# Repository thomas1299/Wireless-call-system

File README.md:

# Wireless-call-system
Die drahtlos angesteuerte Rufanlage dient zum Absetzen eines Notrufs, welche speziell für Menschen mit Einschränkungen der oberen Gliedmaßen entwickelt wurde. Anstatt wie bei herkömmlichen Rufanlagen, wo eine Taste gedrückt werden muss, um den Alarm auszulösen, erfolgt bei dieser Rufanlage die Alarmauslösung über Messung der Temperatur. Die Rufanlage ist in der Lage durch Messung der Temperatur zu erkennen, ob der Sensor zwischen die Lippen genommen wurde oder nicht, um so einen Alarm auszulösen. Der Alarm wird am Basisgerät, an welchem der Temperatursensor angeschlossen ist und am mobilen Empfangsgerät ausgelöst.

Die Alarmauslösung auf beiden Geräten erfolgt innerhalb von 500 ms ab dem Berühren des Sensors durch die Lippen und die Reichweite der Funkverbindung beträgt mindestens 100 m im Freien. Beide Geräte können mit einem Li-Ionen-Akku der Größe 18650 mit 3,7 V versorgt werden.

Die Rufanlage wurde so entwickelt dass diese möglichst Kostengünstig und einfach nachzubauen ist.

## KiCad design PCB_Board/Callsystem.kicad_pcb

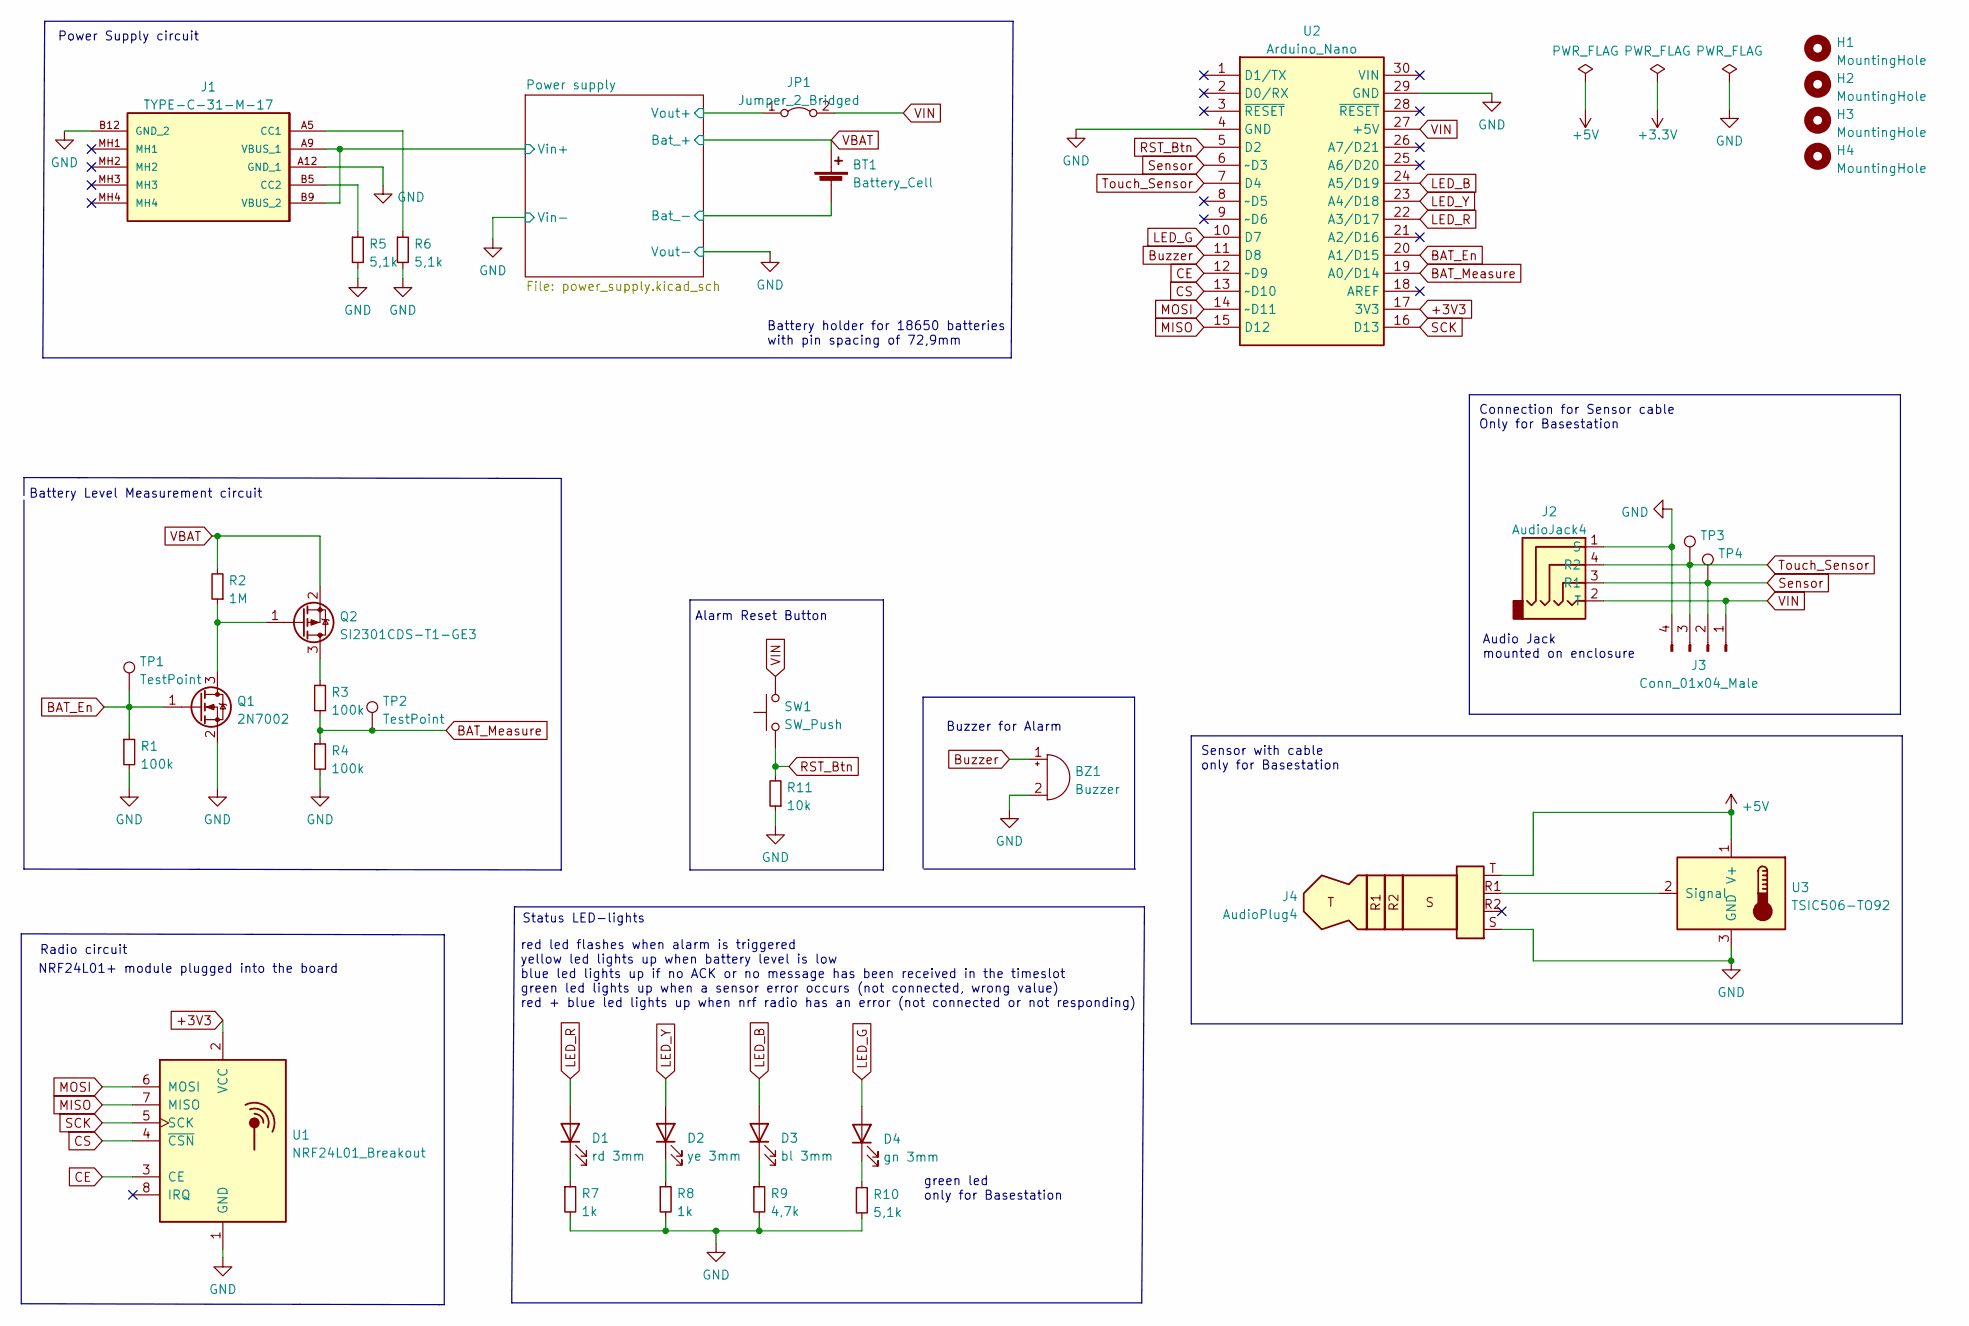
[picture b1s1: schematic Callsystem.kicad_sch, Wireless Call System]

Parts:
BT1: Battery_Cell; BatteryHolder_MPD_BH-18650-PC2
BZ1: Buzzer; Buzzer_12x9.5RM7.6; LCSC C96222
D1: rd 3mm; PinHeader_1x02_P2.54mm_Vertical; LCSC C234182
D2: ye 3mm; PinHeader_1x02_P2.54mm_Vertical; LCSC C234182
D3: bl 3mm; PinHeader_1x02_P2.54mm_Vertical; LCSC C234182
D4: gn 3mm; PinHeader_1x02_P2.54mm_Vertical; LCSC C234182
H1, H2, H3, H4: MountingHole; MountingHole_3.2mm_M3
J1: TYPE-C-31-M-17; TYPEC31M17_new; MANUFACTURER_PART_NUMBER TYPE-C-31-M-17; LCSC C283540
J2: AudioJack4; PinHeader_1x04_P2.54mm_Vertical
J3: Conn_01x04_Male; PinHeader_1x04_P2.54mm_Vertical; LCSC C2905435
J4: AudioPlug4
JP1: Jumper_2_Bridged; PinHeader_1x02_P2.54mm_Vertical; LCSC C234182
Q1: 2N7002; SOT-23; LCSC C8545
Q2: SI2301CDS-T1-GE3; SOT-23; LCSC C10487
R1, R3, R4: 100k; R_0805_2012Metric; LCSC C149504
R2: 1M; R_0805_2012Metric; LCSC C17514
R5, R6, R10: 5,1k; R_0805_2012Metric; LCSC C27834
R7, R8: 1k; R_0805_2012Metric; LCSC C17513
R9: 4,7k; R_0805_2012Metric; LCSC C17673
R11: 10k; R_0805_2012Metric; LCSC C17414
SW1: SW_Push; PinHeader_1x02_P2.54mm_Vertical; LCSC C234182
TP1, TP2, TP3, TP4: TestPoint; TestPoint_Pad_D1.0mm
U1: NRF24L01_Breakout; nRF24L01_LNA_Module; LCSC C239344
U2: Arduino_Nano
U3: TSIC506-TO92; TO-92_Inline

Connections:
+3V3: U1.2 (VCC), U2.17 (3V3)
/Power supply/Bat_-: BT1.2 (-); also elsewhere on the board
/Power supply/Vin+: J1.A9 (VBUS_1), J1.B9 (VBUS_2); also elsewhere on the board
/Power supply/Vout+: JP1.1 (A); also elsewhere on the board
BAT_En: Q1.1 (G), R1.1, TP1.1, U2.20 (A1/D15)
BAT_Measure: R3.2, R4.1, TP2.1, U2.19 (A0/D14)
Buzzer: BZ1.1 (-), U2.11 (D8)
CE: U1.3 (CE), U2.12 (~D9)
CS: U1.4 (~CSN), U2.13 (~D10)
GND: BZ1.2 (+), J1.A12 (GND_1), J1.B12 (GND_2), J2.1 (S), J3.4, J4.S, Q1.2 (S), R1.2, R4.2, R5.2, R6.2, R7.2, R8.2, R9.2, R10.2, R11.1, U1.1 (GND), U2.4 (GND), U2.29 (GND), U3.3 (GND); also elsewhere on the board
LED_B: D3.2 (A), U2.24 (A5/D19)
LED_G: D4.2 (A), U2.10 (D7)
LED_R: D1.2 (A), U2.22 (A3/D17)
LED_Y: D2.2 (A), U2.23 (A4/D18)
MISO: U1.7 (MISO), U2.15 (D12)
MOSI: U1.6 (MOSI), U2.14 (~D11)
unnamed: D1.1 (K), R7.1
unnamed: D2.1 (K), R8.1
unnamed: D3.1 (K), R9.1
unnamed: D4.1 (K), R10.1
unnamed: J1.A5 (CC1), R6.1
unnamed: J1.B5 (CC2), R5.1
unnamed: J4.R1, U3.2 (Signal)
unnamed: J4.T, U3.1 (V+)
unnamed: Q1.3 (D), Q2.1 (G), R2.1
unnamed: Q2.3 (D), R3.1
RST_Btn: R11.2, SW1.1, U2.5 (D2)
SCK: U1.5 (SCK), U2.16 (D13)
Sensor: J2.3 (R1), J3.2, TP4.1, U2.6 (~D3)
Touch_Sensor: J2.4 (R2), J3.3, TP3.1, U2.7 (D4)
VBAT: BT1.1 (+), Q2.2 (S), R2.2; also elsewhere on the board
VIN: J2.2 (T), J3.1, JP1.2 (B), SW1.2, U2.27 (+5V)

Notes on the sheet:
Radio circuit
Status LED-lights
Buzzer for Alarm
red led flashes when alarm is triggered yellow led lights up when battery level is low blue led lights up if no ACK or no message has been received in the timeslot green led lights up when a sensor error occurs (not connected, wrong value) red + blue led lights up when nrf radio has an error (not c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
NRF24L01+ module plugged into the board
Battery Level Measurement circuit
Sensor with cable only for Basestation
Battery holder for 18650 batteries with pin spacing of 72,9mm
Audio Jack mounted on enclosure
Power Supply circuit
green led only for Basestation
Connection for Sensor cable Only for Basestation
Alarm Reset Button

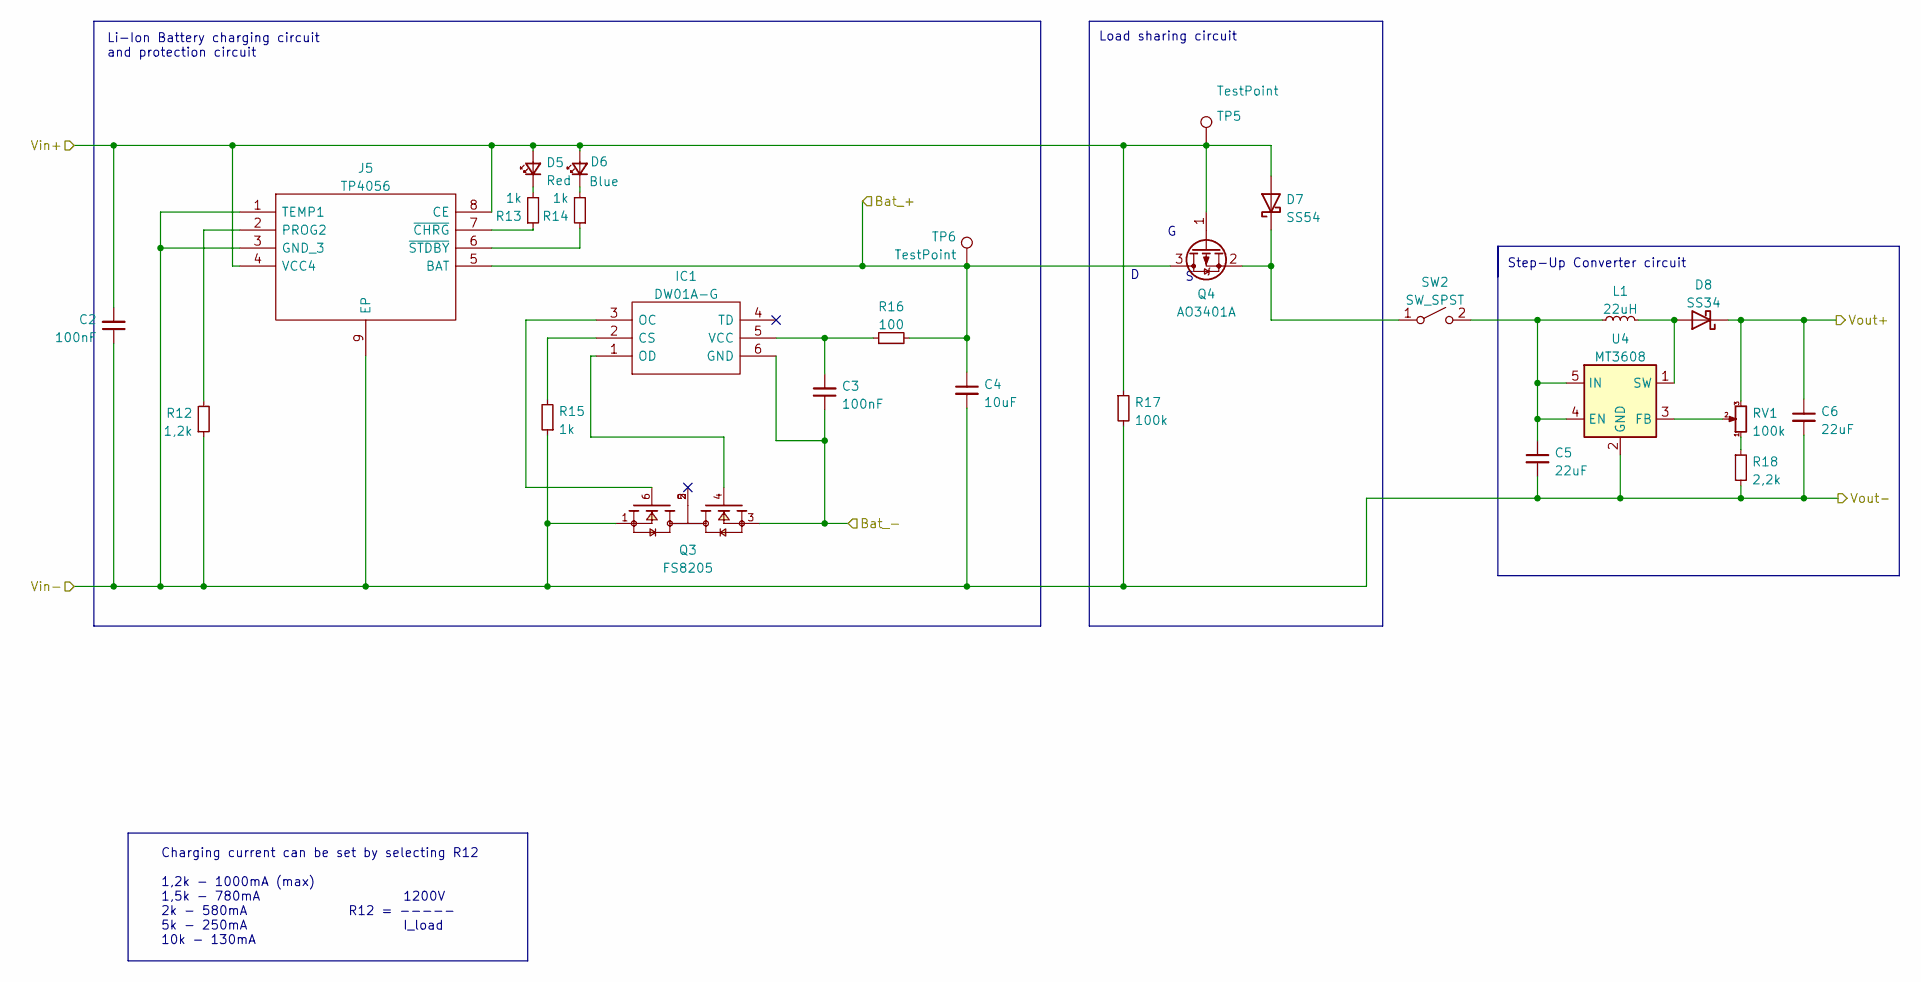
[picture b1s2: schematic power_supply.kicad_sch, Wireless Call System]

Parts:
C2, C3: 100nF; C_0805_2012Metric; LCSC C49678
C4: 10uF; C_0805_2012Metric; LCSC C15850
C5, C6: 22uF; C_1206_3216Metric; LCSC C12891
D5: Red; LED_0805_2012Metric; LCSC C84256
D6: Blue; LED_0805_2012Metric; LCSC C34499
D7: SS54; D_SMA; LCSC C22452
D8: SS34; D_SMA; LCSC C8678
IC1: DW01A-G; SOT-23-6; Manufacturer_Part_Number DW01A-G; LCSC C61503
J5: TP4056; SOP127P600X175-9N; Manufacturer_Part_Number TP4056; LCSC C16581
L1: 22uH; SLO0630H; LCSC C207843
Q3: FS8205; SOT-23-6; PARTREV 1.9; LCSC C908265
Q4: AO3401A; SOT-23; LCSC C15127
R12: 1,2k; R_0805_2012Metric; LCSC C17379
R13, R14, R15: 1k; R_0805_2012Metric; LCSC C17513
R16: 100; R_0805_2012Metric; LCSC C17408
R17: 100k; R_0805_2012Metric
R18: 2,2k; R_0805_2012Metric; LCSC C17520
RV1: 100k; Potentiometer_Bourns_3296W_Vertical; LCSC C118963
SW2: SW_SPST; PinHeader_1x02_P2.54mm_Vertical; LCSC C234182
TP5, TP6: TestPoint; TestPoint_Pad_D1.0mm
U4: MT3608; SOT-23-6; LCSC C84817

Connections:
/Power supply/Bat_-: C3.1, IC1.6 (GND), Q3.3; also elsewhere on the board
/Power supply/Vin+: C2.2, D5.2 (A), D6.2 (A), D7.2 (A), J5.4 (VCC4), J5.8 (CE), Q4.1 (G), R17.1, TP5.1; also elsewhere on the board
/Power supply/Vout+: C6.1, D8.1 (K), RV1.3; also elsewhere on the board
GND: C2.1, C4.2, C5.2, C6.2, J5.1 (TEMP1), J5.3 (GND_3), J5.9 (EP), Q3.1, R12.1, R15.1, R17.2, R18.2, U4.2 (GND); also elsewhere on the board
unnamed: C3.2, IC1.5 (VCC), R16.1
unnamed: C5.1, L1.1, SW2.2 (B), U4.4 (EN), U4.5 (IN)
unnamed: D5.1 (K), R13.2
unnamed: D6.1 (K), R14.2
unnamed: D7.1 (K), Q4.2 (S), SW2.1 (A)
unnamed: D8.2 (A), L1.2, U4.1 (SW)
unnamed: IC1.1 (OD), Q3.4
unnamed: IC1.2 (CS), R15.2
unnamed: IC1.3 (OC), Q3.6
unnamed: J5.2 (PROG2), R12.2
unnamed: J5.6 (~STDBY), R14.1
unnamed: J5.7 (~CHRG), R13.1
unnamed: R18.1, RV1.1
unnamed: RV1.2, U4.3 (FB)
VBAT: C4.1, J5.5 (BAT), Q4.3 (D), R16.2, TP6.1; also elsewhere on the board

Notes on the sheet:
Load sharing circuit
Charging current can be set by selecting R12 1,2k - 1000mA (max) 1,5k - 780mA 2k - 580mA 5k - 250mA 10k - 130mA
Step-Up Converter circuit
Li-Ion Battery charging circuit and protection circuit
1200V R12 = ----- I_load

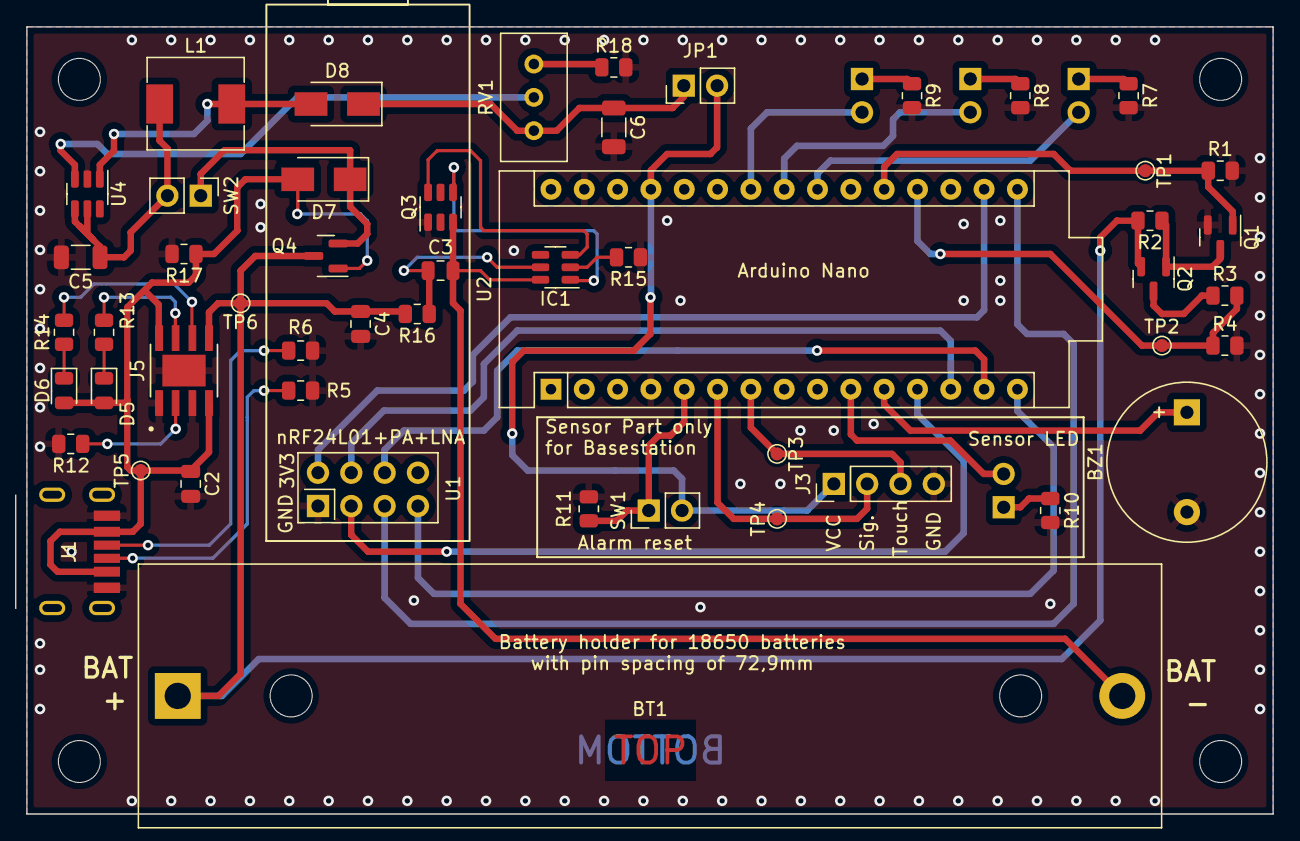
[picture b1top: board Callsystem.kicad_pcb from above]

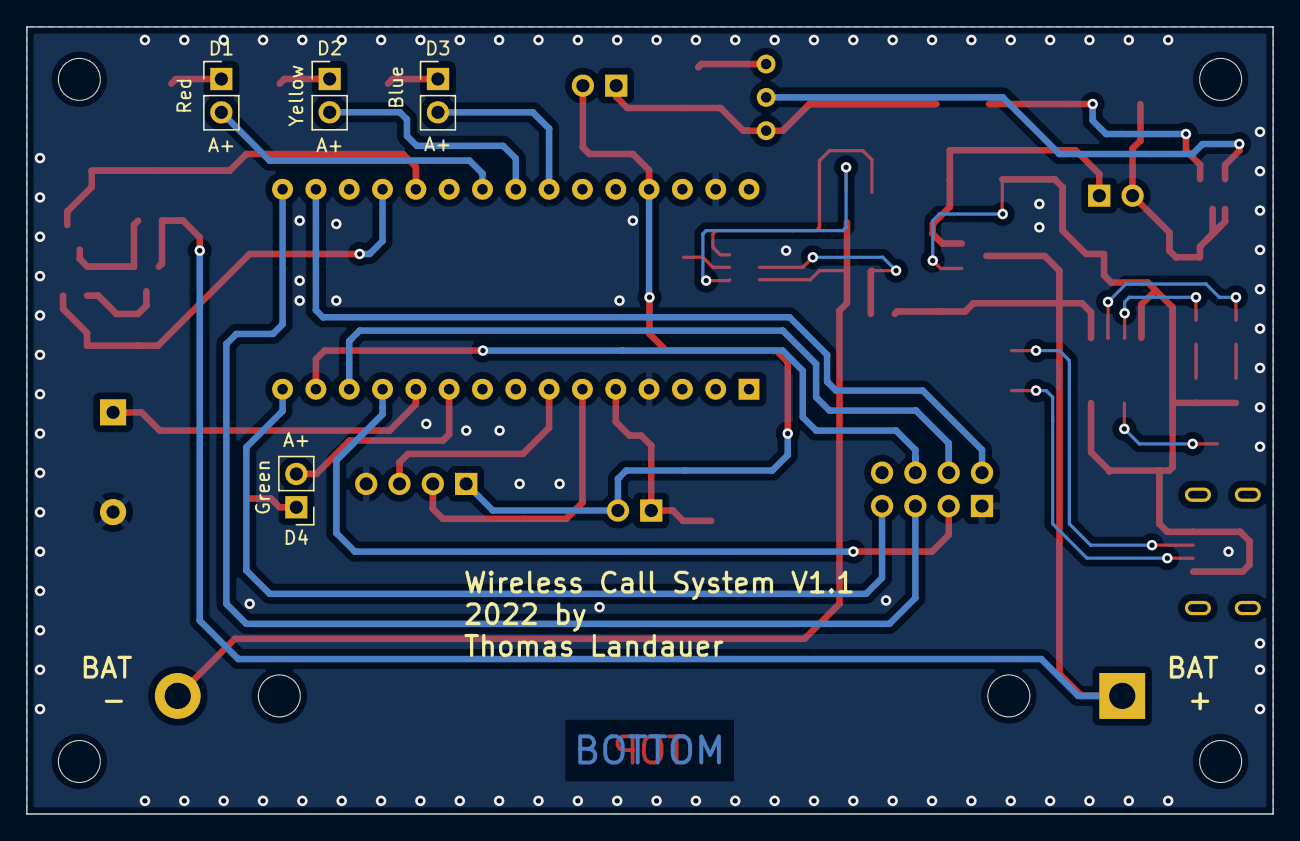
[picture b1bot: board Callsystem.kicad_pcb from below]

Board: 2 copper layers, 95.0 x 60.0 mm, 59 parts (4 on the bottom side), 44 nets.

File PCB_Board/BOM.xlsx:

Comment | Designator | Footprint | LCSC
Buzzer | BZ1 | Buzzer_Beeper:Buzzer_12x9.5RM7.6 | C96222
100nF | C2,C3 | Capacitor_SMD:C_0805_2012Metric | C49678
10uF | C4 | Capacitor_SMD:C_0805_2012Metric | C15850
22uF | C5,C6 | Capacitor_SMD:C_1206_3216Metric | C12891
Red | D5 | LED_SMD:LED_0805_2012Metric | C84256
Blue | D6 | LED_SMD:LED_0805_2012Metric | C34499
SS54 | D7 | Diode_SMD:D_SMA | C22452
SS34 | D8 | Diode_SMD:D_SMA | C8678
DW01A-G | IC1 | Package_TO_SOT_SMD:SOT-23-6 | C61503
TYPE-C-31-M-17 | J1 | project_library:TYPEC31M17_new | C283540
Conn_01x04_Male | J3 | Connector_PinHeader_2.54mm:PinHeader_1x04_P2.54mm_Vertical | C2905435
TP4056 | J5 | project_library:SOP127P600X175-9N | C16581
Jumper_2_Bridged | JP1 | Connector_PinHeader_2.54mm:PinHeader_1x02_P2.54mm_Vertical | C234182
22uH | L1 | project_library:SLO0630H | C207843
2N7002 | Q1 | Package_TO_SOT_SMD:SOT-23 | C8545
SI2301CDS-T1-GE3 | Q2 | Package_TO_SOT_SMD:SOT-23 | C10487
FS8205 | Q3 | Package_TO_SOT_SMD:SOT-23-6 | C908265
AO3401A | Q4 | Package_TO_SOT_SMD:SOT-23 | C15127
100k | R1,R3,R4,R17 | Resistor_SMD:R_0805_2012Metric | C149504
10k | R11 | Resistor_SMD:R_0805_2012Metric | C17414
1,2k | R12 | Resistor_SMD:R_0805_2012Metric | C17379
100 | R16 | Resistor_SMD:R_0805_2012Metric | C17408
2,2k | R18 | Resistor_SMD:R_0805_2012Metric | C17520
1M | R2 | Resistor_SMD:R_0805_2012Metric | C17514
5,1k | R5,R6,R10 | Resistor_SMD:R_0805_2012Metric | C27834
1k | R7,R8,R13,R14,R15 | Resistor_SMD:R_0805_2012Metric | C17513
4,7k | R9 | Resistor_SMD:R_0805_2012Metric | C17673
100k | RV1 | Potentiometer_THT:Potentiometer_Bourns_3296W_Vertical | C118963
SW_Push | SW1 | Connector_PinHeader_2.54mm:PinHeader_1x02_P2.54mm_Vertical | C234182
SW_SPST | SW2 | Connector_PinHeader_2.54mm:PinHeader_1x02_P2.54mm_Vertical | C234182
NRF24L01_Breakout | U1 | project_library:nRF24L01_LNA_Module | C239344
MT3608 | U4 | Package_TO_SOT_SMD:SOT-23-6 | C84817

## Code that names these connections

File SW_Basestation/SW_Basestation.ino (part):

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#define BATTERYCHKINTERVAL 300 // define battery check period; multiple times of 1s (1min = 60*1s)
#define NUM_SAMPLES 10 // defines number of ADC samples for battery voltage measurement
#define BATTERYTHRESHOLD 3.0 // defines the threshold for an empty battery
#define USEBUZZER 1 // set to 1 to enable Buzzer Audio output

#if DEBUG == 1
#define debug(x) Serial.print(x)
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const int ResetButton = 2;

// TSic506 Variables
const uint8_t TSic_Pin = 3; // Signal Pin of TSIC-Sensor
TSIC Sensorx(TSic_Pin);
volatile float TSic_temp = NAN; // Temperature in °C
volatile bool TSic_newData = 0; // flag to indicate new data
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const int led_yellow = 18;
const int led_blue = 19;
const int led_green = 7; // correct to 7
// Buzzer pin
const int Buzzer = 8;

// Variables for Battery measurement
const int Bat_measure = A0; // Analog Pin A0
const int Bat_En = 15; // Digital Pin 15
float battery_voltage = 0;

// Error values
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    pinMode(led_yellow, OUTPUT);
    pinMode(led_blue, OUTPUT);
    pinMode(led_green, OUTPUT);
    pinMode(Bat_En, OUTPUT);
    pinMode(Buzzer, OUTPUT);

    digitalWrite(Buzzer, LOW);
    digitalWrite(led_red, LOW);
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        // If TSIC-ISR has not been executed since the last transmission, the sensor is not connected.
        if (Alarm_flag == 0) {
            if (TSic_isrCount == 0) {
                TSic_error = 1; // sensor not connected!
            } else {
                TSic_isrCount = 0;
            }
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// Interrupt service routine to read data from TSIC-Sensor
void TSic_isr(void)
{
    volatile uint16_t TSic_raw = 0; // Variable for saving the 10-bit raw data from the TSic sensor
    volatile uint8_t ReadError = 0;
    /*start critical timing */
    ReadError = Sensorx.TSic_ReadData(&TSic_raw);
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
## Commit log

2023-01-03 Init commit
2023-01-08 upload manual

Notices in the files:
SW_Basestation/SW_Basestation.ino:
This program is free software: you can redistribute it and/or modify
it under the terms of the GNU General Public License as published by
the Free Software Foundation, either version 3 of the License, or
(at your option) any later version.
